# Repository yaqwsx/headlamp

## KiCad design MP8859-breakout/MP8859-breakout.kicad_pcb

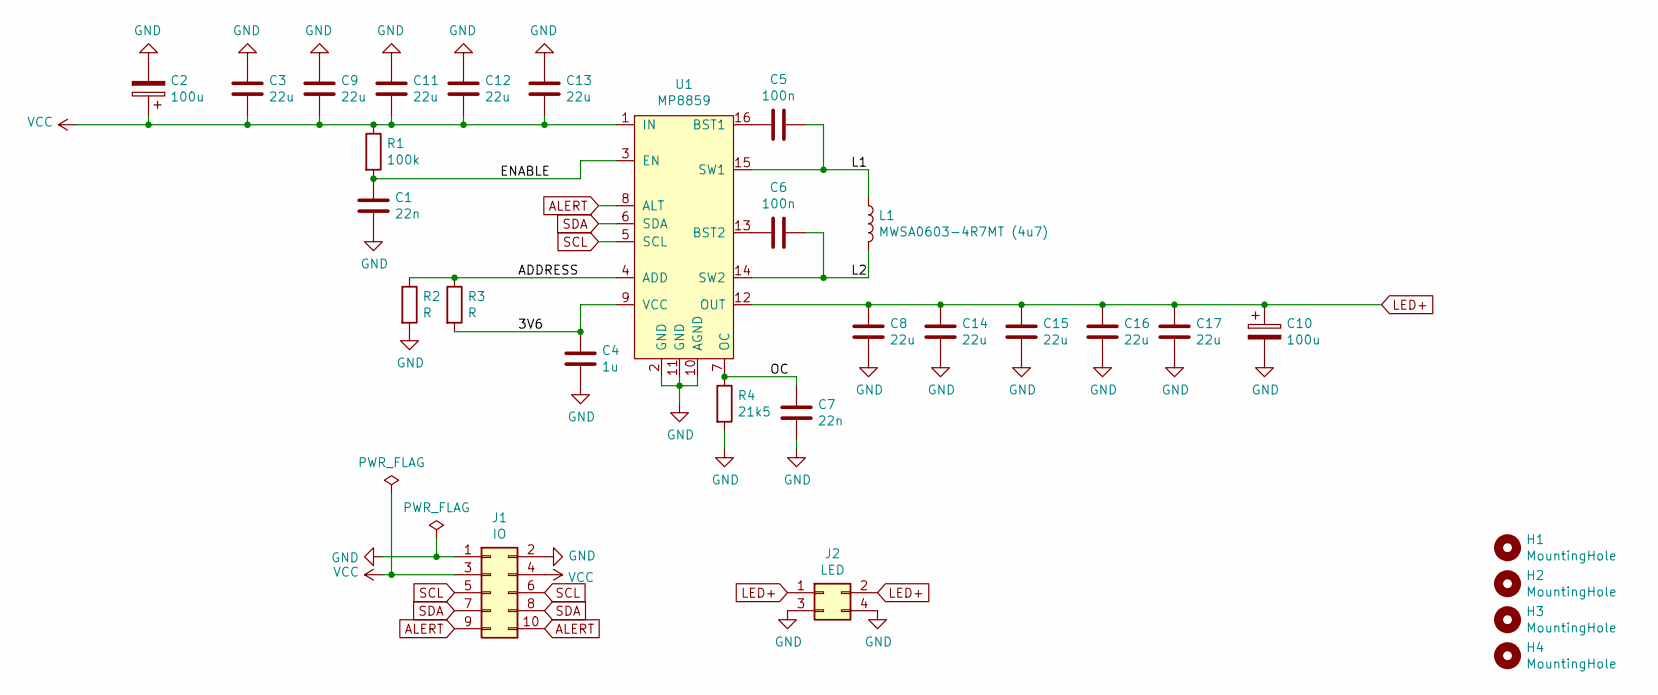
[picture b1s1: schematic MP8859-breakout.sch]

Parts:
C1, C7: 22n; C_0402_1005Metric; LCSC C1532
C2, C10: 100u; CP_EIA-3528-21_Kemet-B; LCSC C16133
C3, C8, C9, C11, C12, C13, C14, C15, C16, C17: 22u; C_0805_2012Metric; LCSC C45783
C4: 1u; C_0402_1005Metric; LCSC C52923
C5, C6: 100n; C_0402_1005Metric; LCSC C1525
H1, H2, H3, H4: MountingHole; MountingHole_2.2mm_M2
J1: IO; PinHeader_2x05_P2.54mm_Vertical
J2: LED; PinHeader_2x02_P2.54mm_Vertical
L1: MWSA0603-4R7MT (4u7); MWSA0603; LCSC C132139
R1: 100k; R_0402_1005Metric; LCSC C25741
R2, R3: R; R_0603_1608Metric
R4: 21k5; R_0402_1005Metric; LCSC C25768
U1: MP8859

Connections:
/3V6: C4.1, R3.2, U1.9 (VCC)
/ADDRESS: R2.1, R3.1, U1.4 (ADD)
/ENABLE: C1.1, R1.2, U1.3 (EN)
/L1: C5.1, L1.1, U1.15 (SW1)
/L2: C6.1, L1.2, U1.14 (SW2)
/OC: C7.1, R4.1, U1.7 (OC)
ALERT: J1.9, J1.10, U1.8 (ALT)
GND: C1.2, C2.2, C3.1, C4.2, C7.2, C8.2, C9.1, C10.2, C11.1, C12.1, C13.1, C14.2, C15.2, C16.2, C17.2, J1.1, J1.2, J2.3, J2.4, R2.2, R4.2, U1.2 (GND), U1.10 (AGND), U1.11 (GND)
LED+: C8.1, C10.1, C14.1, C15.1, C16.1, C17.1, J2.1, J2.2, U1.12 (OUT)
unnamed: C5.2, U1.16 (BST1)
unnamed: C6.2, U1.13 (BST2)
SCL: J1.5, J1.6, U1.5 (SCL)
SDA: J1.7, J1.8, U1.6 (SDA)
VCC: C2.1, C3.2, C9.2, C11.2, C12.2, C13.2, J1.3, J1.4, R1.1, U1.1 (IN)

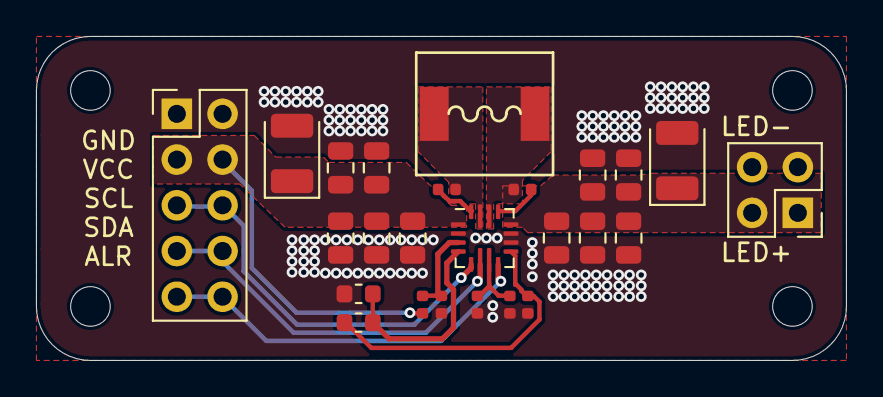
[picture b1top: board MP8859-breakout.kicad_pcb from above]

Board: 2 copper layers, 45.0 x 18.0 mm, 29 parts (0 on the bottom side), 14 nets.

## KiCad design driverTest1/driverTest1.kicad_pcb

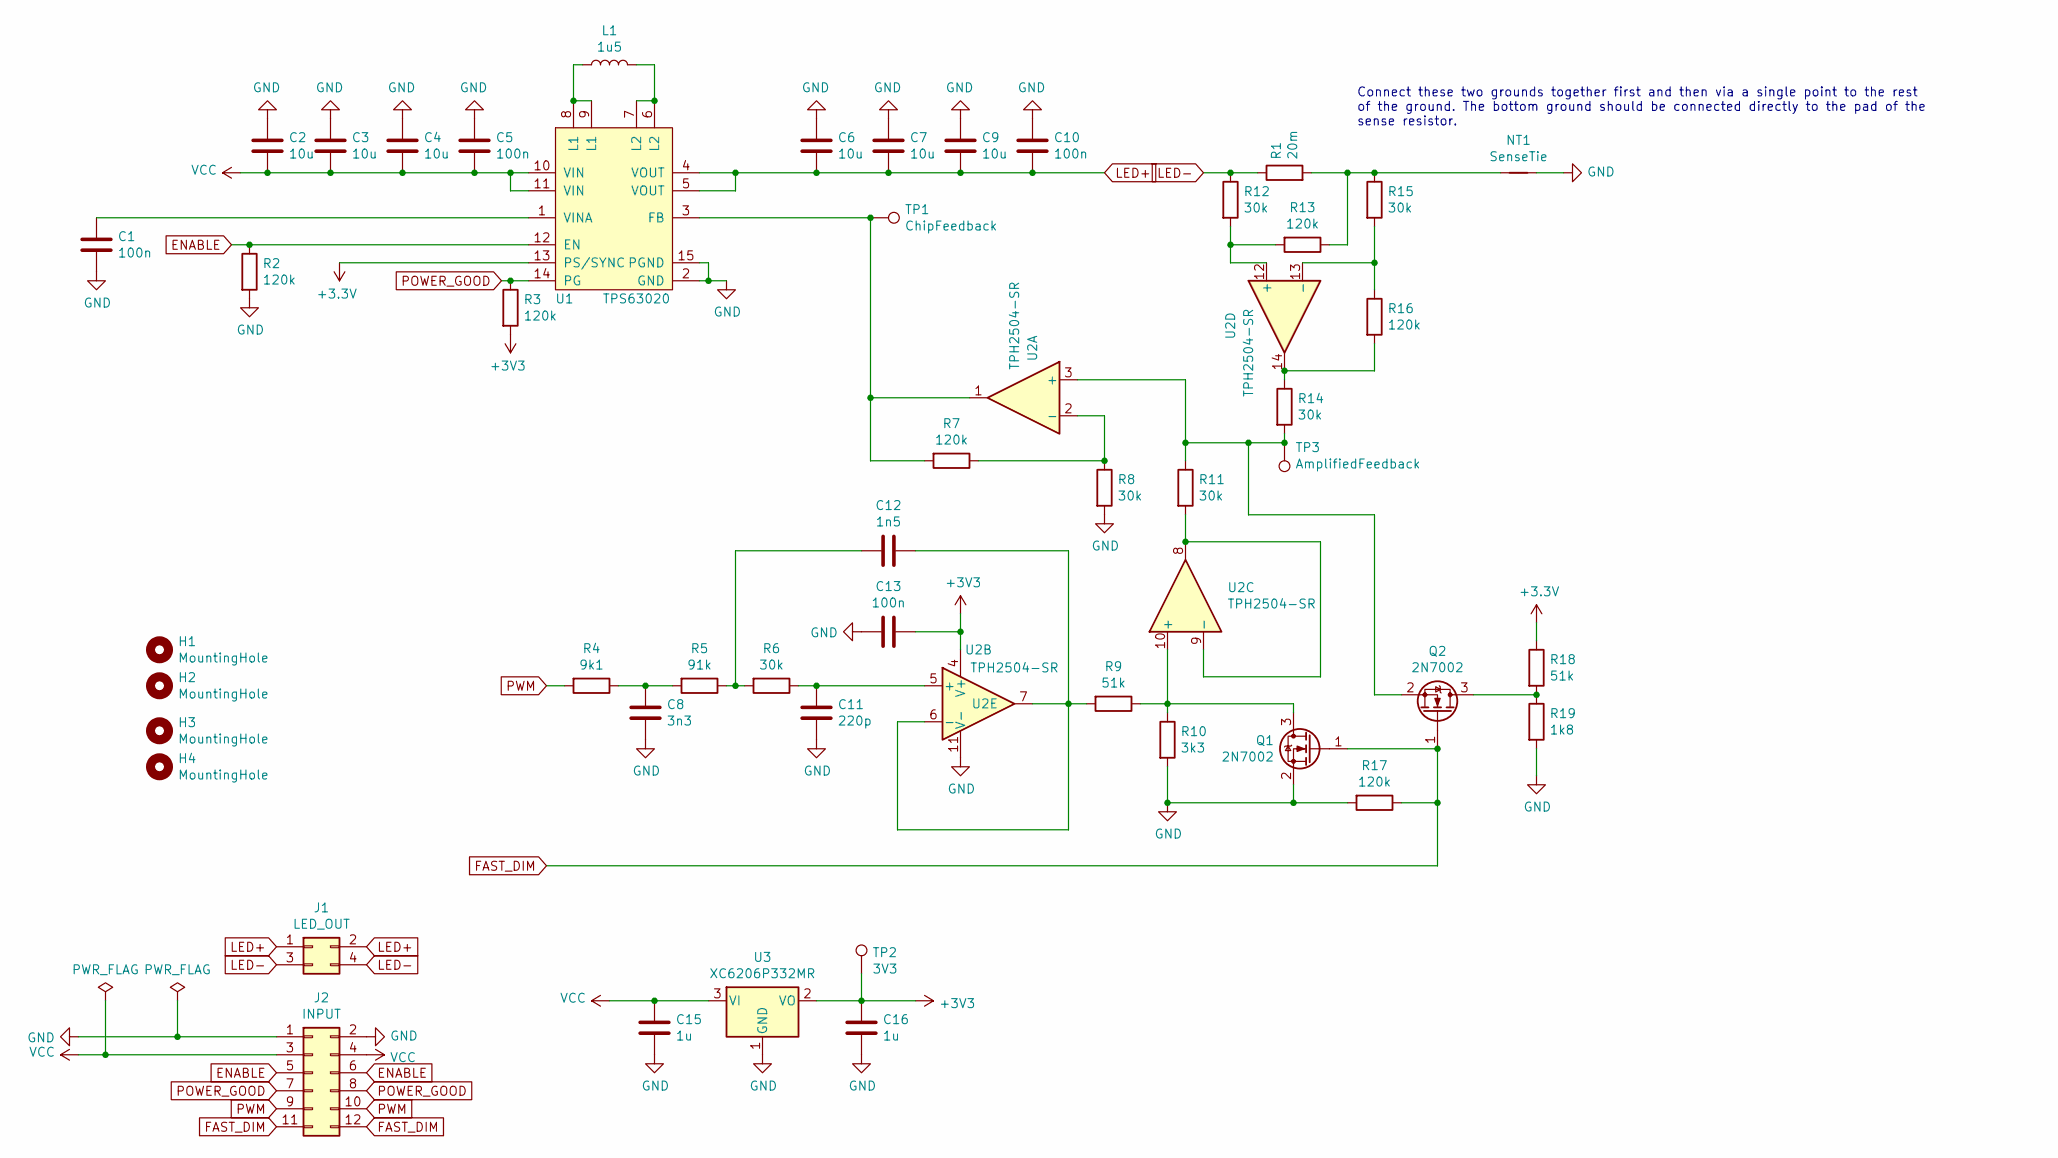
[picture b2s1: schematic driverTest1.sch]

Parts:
C1, C5, C10, C13: 100n; C_0603_1608Metric; LCSC C14663
C2, C3, C4, C6, C7, C9: 10u; C_0603_1608Metric; LCSC C96446
C8: 3n3; C_0603_1608Metric; LCSC C1613
C11: 220p; C_0603_1608Metric; LCSC C1603
C12: 1n5; C_0603_1608Metric; LCSC C1595
C15, C16: 1u; C_0402_1005Metric; LCSC C52923
H1, H2, H3, H4: MountingHole; MountingHole_2.2mm_M2
J1: LED_OUT; PinHeader_2x02_P2.54mm_Vertical
J2: INPUT; PinHeader_2x06_P2.54mm_Vertical
L1: 1u5; MWSA0518; LCSC C408344
NT1: SenseTie; NetTie-2_SMD_Pad0.5mm
Q1, Q2: 2N7002; SOT-23; LCSC C8545
R1: 20m; R_0805_2012Metric; LCSC C92740
R2, R3, R7, R13, R16, R17: 120k; R_0603_1608Metric; LCSC C25808
R4: 9k1; R_0603_1608Metric; LCSC C23260
R5: 91k; R_0603_1608Metric; LCSC C23265
R6, R8, R11, R12, R14, R15: 30k; R_0603_1608Metric; LCSC C22984
R9, R18: 51k; R_0603_1608Metric; LCSC C23196
R10: 3k3; R_0603_1608Metric; LCSC C22978
R19: 1k8; R_0603_1608Metric; LCSC C4177
TP1: ChipFeedback; TestPoint_THTPad_1.5x1.5mm_Drill0.7mm
TP2: 3V3; TestPoint_THTPad_1.5x1.5mm_Drill0.7mm
TP3: AmplifiedFeedback; TestPoint_THTPad_1.5x1.5mm_Drill0.7mm
U1: TPS63020; LCSC C15483
U2: TPH2504-SR; SOIC-14_3.9x8.7mm_P1.27mm; LCSC C115918
U3: XC6206P332MR; SOT-23; LCSC C5446

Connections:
ENABLE: J2.5, J2.6, R2.1, U1.12 (EN)
FAST_DIM: J2.11, J2.12, Q1.1 (G), Q2.1 (G), R17.1
GND: C1.1, C2.1, C3.1, C4.1, C5.1, C6.1, C7.1, C8.1, C9.1, C10.1, C11.1, C13.2, C15.2, C16.2, J2.1, J2.2, NT1.2, Q1.2 (S), R2.2, R8.2, R10.2, R17.2, R19.2, U1.2 (GND), U1.15 (PGND), U2.11 (V-), U3.1 (GND)
LED+: C6.2, C7.2, C9.2, C10.2, J1.1, J1.2, U1.4 (VOUT), U1.5 (VOUT)
LED-: J1.3, J1.4, R1.1, R12.1
unnamed: C1.2, U1.1 (VINA)
unnamed: C8.2, R4.1, R5.2
unnamed: C11.2, R6.1, U2.5 (+)
unnamed: C12.1, R9.2, U2.6 (-), U2.7
unnamed: C12.2, R5.1, R6.2
unnamed: L1.1, U1.8 (L1), U1.9 (L1)
unnamed: L1.2, U1.6 (L2), U1.7 (L2)
unnamed: NT1.1, R1.2, R13.1, R15.1
unnamed: Q1.3 (D), R9.1, R10.1, U2.10 (+)
unnamed: Q2.2 (S), R11.1, R14.2, TP3.1, U2.3 (+)
unnamed: Q2.3 (D), R18.2, R19.1
unnamed: R7.1, R8.1, U2.2 (-)
unnamed: R7.2, TP1.1, U1.3 (FB), U2.1
unnamed: R11.2, U2.8, U2.9 (-)
unnamed: R12.2, R13.2, U2.12 (+)
unnamed: R14.1, R16.2, U2.14
unnamed: R15.2, R16.1, U2.13 (-)
POWER_GOOD: J2.7, J2.8, R3.1, U1.14 (PG)
PWM: J2.9, J2.10, R4.2
VCC: C2.2, C3.2, C4.2, C5.2, C15.1, J2.3, J2.4, U1.10 (VIN), U1.11 (VIN), U3.3 (VI)

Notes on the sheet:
Connect these two grounds together first and then via a single point to the rest of the ground. The bottom ground should be connected directly to the pad of the sense resistor.

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
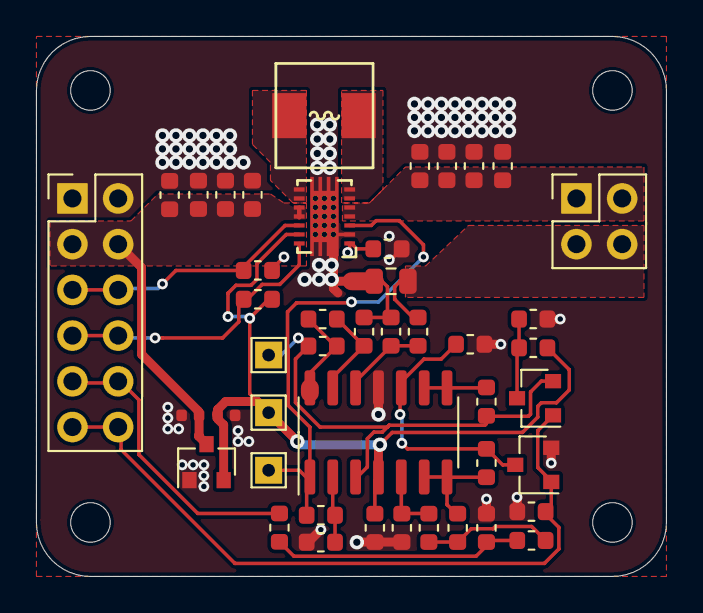
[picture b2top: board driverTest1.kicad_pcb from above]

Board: 2 copper layers, 35.0 x 30.0 mm, 50 parts (0 on the bottom side), 26 nets.

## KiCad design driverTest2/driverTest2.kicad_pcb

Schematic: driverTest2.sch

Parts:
C1: 10n; C_0603_1608Metric_Pad1.05x0.95mm_HandSolder
C2: 100n; C_0603_1608Metric_Pad1.05x0.95mm_HandSolder
C3: 470n; C_0603_1608Metric_Pad1.05x0.95mm_HandSolder
D1: FML340A-W; DO-214AC
J1: INPUT; PinHeader_2x04_P2.54mm_Vertical
J2: LED_OUTPUT; PinHeader_2x02_P2.54mm_Vertical
L1: SRU1038-100Y; L_Bourns-SRU1028_10.0x10.0mm
R1: KDV12FR050ET; R_1206_3216Metric
U1: RT8498; SOT-23-6_Handsoldering

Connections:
ACTL: C1.1, J1.7, J1.8, U1.4
DCTL: J1.5, J1.6, U1.3
GND: C1.2, C2.2, J1.3, J1.4, U1.2
LED+: J2.1, J2.2, R1.2, U1.6
LED-: C3.1, J1.1, J1.2, J2.3, J2.4, L1.1
unnamed: C2.1, C3.2, D1.1 (K), R1.1, U1.5
unnamed: D1.2 (A), L1.2, U1.1

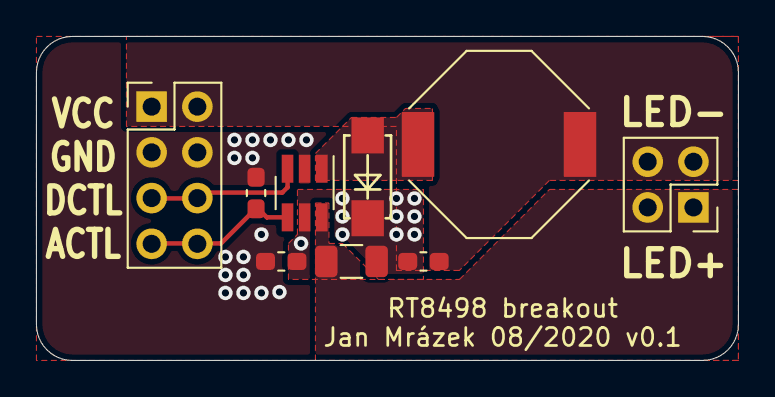
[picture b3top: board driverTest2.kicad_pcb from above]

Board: 2 copper layers, 39.0 x 18.0 mm, 9 parts (0 on the bottom side), 7 nets.

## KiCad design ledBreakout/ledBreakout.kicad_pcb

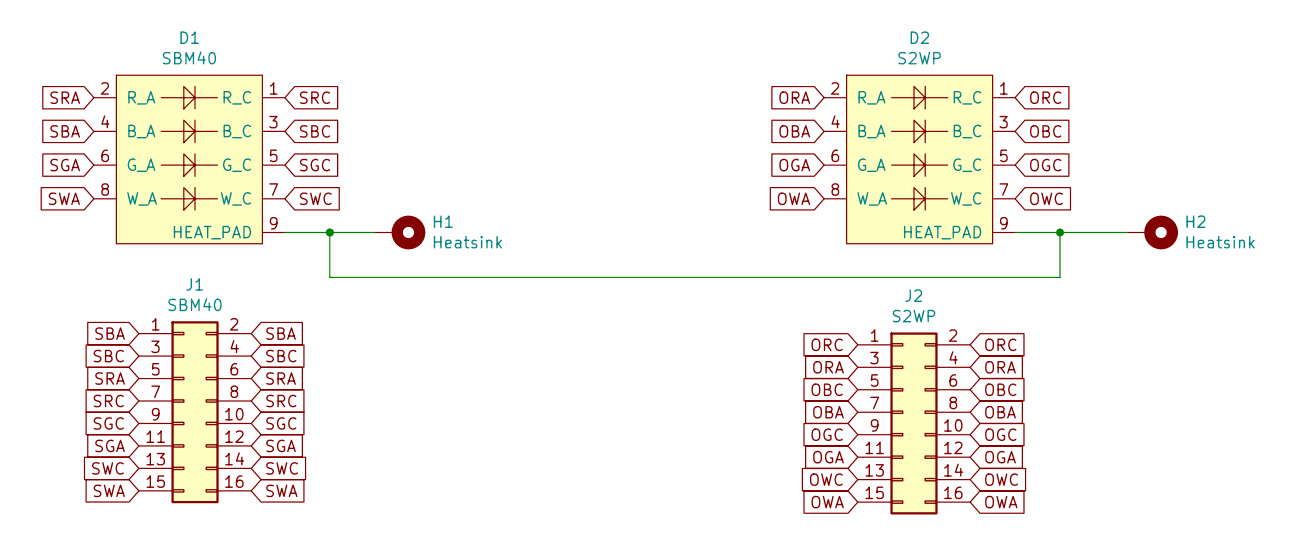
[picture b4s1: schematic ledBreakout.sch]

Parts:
D1: SBM40
D2: S2WP; Osram LE RTDUW S2WP
H1, H2: Heatsink; HeatSinkMount
J1: SBM40; PinHeader_2x08_P2.54mm_Vertical
J2: S2WP; PinHeader_2x08_P2.54mm_Vertical

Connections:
unnamed: D1.9 (HEAT_PAD), D2.9 (HEAT_PAD), H1.1, H2.1
OBA: D2.4 (B_A), J2.7, J2.8
OBC: D2.3 (B_C), J2.5, J2.6
OGA: D2.6 (G_A), J2.11, J2.12
OGC: D2.5 (G_C), J2.9, J2.10
ORA: D2.2 (R_A), J2.3, J2.4
ORC: D2.1 (R_C), J2.1, J2.2
OWA: D2.8 (W_A), J2.15, J2.16
OWC: D2.7 (W_C), J2.13, J2.14
SBA: D1.4 (B_A), J1.1, J1.2
SBC: D1.3 (B_C), J1.3, J1.4
SGA: D1.6 (G_A), J1.11, J1.12
SGC: D1.5 (G_C), J1.9, J1.10
SRA: D1.2 (R_A), J1.5, J1.6
SRC: D1.1 (R_C), J1.7, J1.8
SWA: D1.8 (W_A), J1.15, J1.16
SWC: D1.7 (W_C), J1.13, J1.14

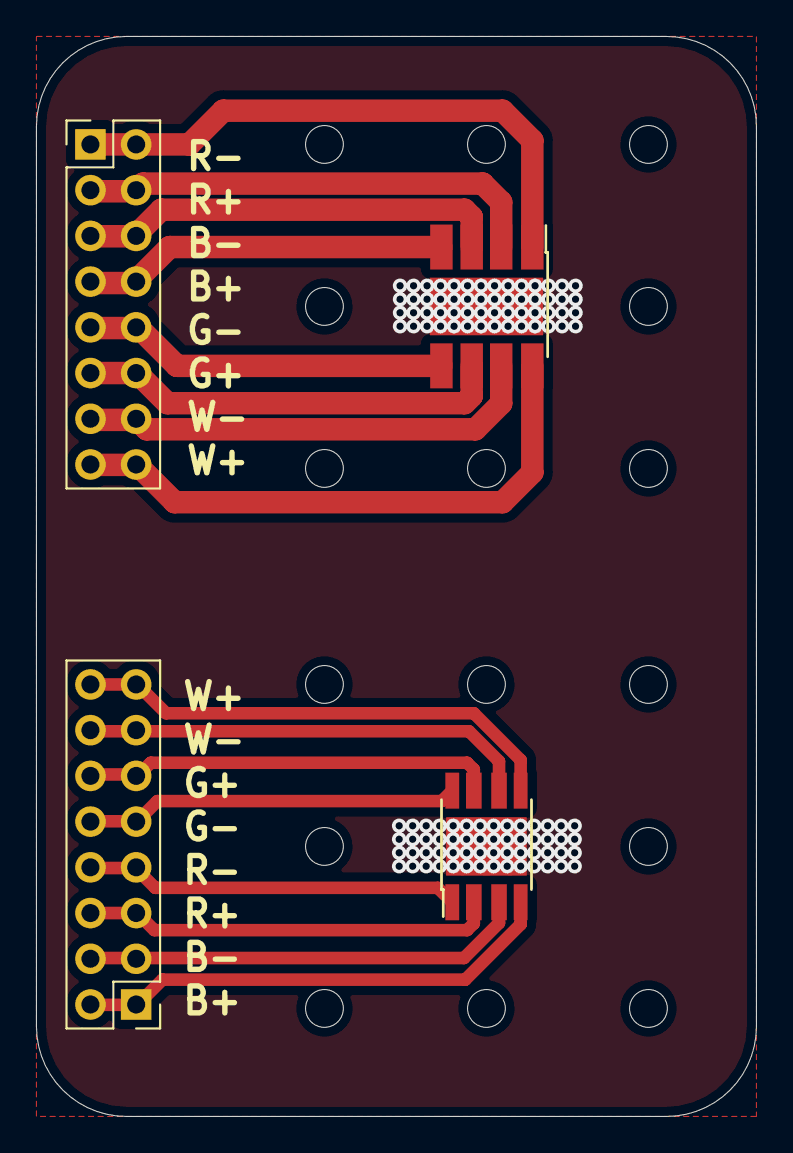
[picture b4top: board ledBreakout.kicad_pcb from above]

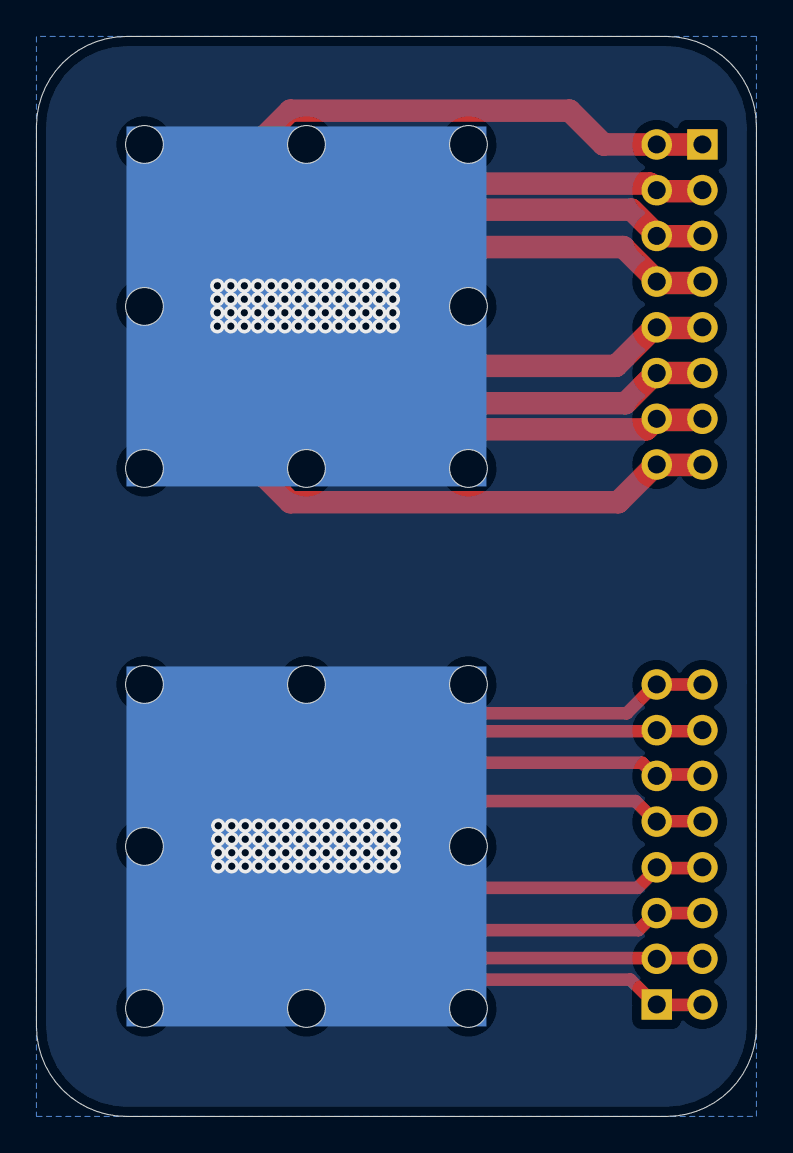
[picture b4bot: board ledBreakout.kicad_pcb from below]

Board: 2 copper layers, 40.0 x 60.0 mm, 6 parts (2 on the bottom side), 17 nets.

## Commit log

2018-10-14 Add component list
2020-07-23 Add led driver schematic draft (without values)
2020-07-24 Add schematics draft of the first driver test
2020-07-24 Add routing note
2020-08-05 Add values, but no suitable (fast enough) OP AMP found.
2020-08-06 Redesign for slower OP AMPs, choose parts
2020-08-07 Fix filter attenuation, add fast dimming input
2020-08-07 Add new schema
2020-08-08 Draft first board layout
2020-08-09 Add RT8498 breakout
2020-08-09 Add MP8859 breakout
2020-08-09 Commit last minute changes
2020-08-11 Tweak assembly data
2020-08-11 Add Makefile
